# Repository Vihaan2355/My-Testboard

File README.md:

# My-Testboard

This repository contains the design files for a custom hardware development and test board built using KiCad. The circuit is designed around a standard LM555 testboard.

# Project Structure
* /CAD - Contains the 3D STEP file (TestBoard.step) of the populated PCB layout and the native project files.
* /GERBERS - Contains the production zip file (Gerbers.zip) required for manufacturing fabrication.
* TestBoard.csv - Bill of Materials (BOM) listing the complete component inventory and sourcing data.
* TestBoard-pos.csv - Component Placement List (CPL) detailing structural coordinate data for assembly alignment.
* TestBoard.pdf - Schematic drawing printout.

# Mechanical and Hardware Design
This project is a bare hardware development and test board. It focuses strictly on circuit traces and signal routing, and it does not feature a physical 3D-printed case, enclosure, or mechanical stand. 

The STEP file provided inside the /CAD folder represents the complete 3D spatial layout of the PCB alongside its mounted components. This file serves as the complete, self-contained physical project assembly to satisfy the 3D modeling submission rule.

# Component Sourcing and Assembly Plan
The circuit utilizes a through-hole design layout. Assembly is split between factory placement and manual desktop soldering:

* Integrated Circuit (U1): LM555CN  chip in a DIP-8 package.
* Potentiometer (RV1): 10K vertical rotary trimmer potentiometer (3386P package). This part is sourced via external vendor channels and will be hand-soldered locally.
* Passive Components (R1-R3, C1-C3, D1): 1K Ohm 1/4W axial resistors, ceramic disc capacitors (10nF and 100nF values), a radial electrolytic capacitor (47uF value), and a 3mm blue indicator LED. These parts are sourced via bulk electronic assortment kits and will be hand-soldered locally.
* Power Interface (J1): 2-pin horizontal screw terminal block featuring 3.5mm pad pitch spacing. This part is sourced via external vendor channels and will be hand-soldered locally.

# Manufacturing Fabrication
The bare boards will be manufactured using standard FR4 fiberglass substrate through JLCPCB using the production zip file in the gerbers directory. Remaining components will be manually populated, soldered, and verified on a test bench post-delivery.

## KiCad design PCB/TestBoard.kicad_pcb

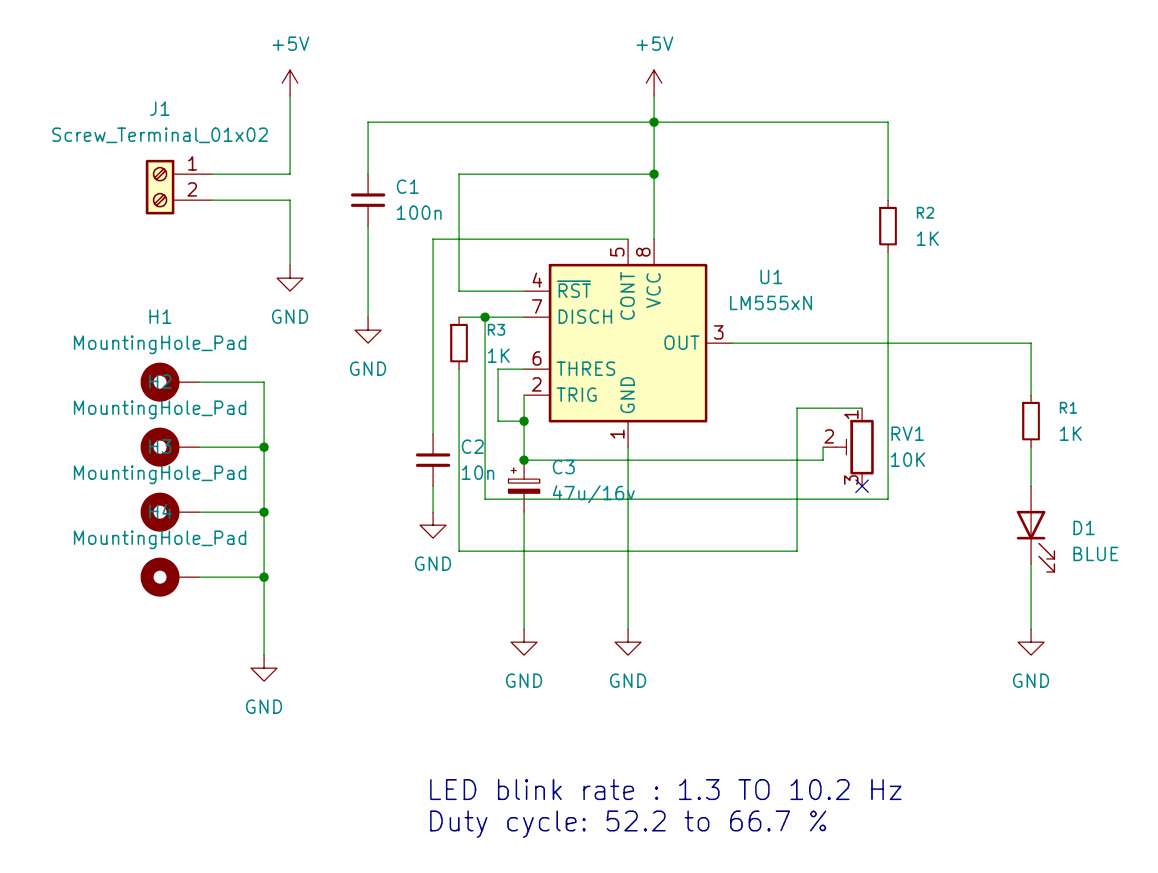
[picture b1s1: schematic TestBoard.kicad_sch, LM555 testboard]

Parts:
C1: 100n; C_Disc_D7.0mm_W2.5mm_P5.00mm
C2: 10n; C_Disc_D7.0mm_W2.5mm_P5.00mm
C3: 47u/16v; CP_Radial_D5.0mm_P2.50mm
D1: BLUE; LED_D3.0mm
H1, H2, H3, H4: MountingHole_Pad; MountingHole_3.2mm_M3_DIN965_Pad
J1: Screw_Terminal_01x02; TerminalBlock_Phoenix_PT-1,5-2-3.5-H_1x02_P3.50mm_Horizontal
R1, R2, R3: 1K; R_Axial_DIN0207_L6.3mm_D2.5mm_P10.16mm_Horizontal
RV1: 10K; Potentiometer_Bourns_3386P_Vertical
U1: LM555xN; DIP-8_W7.62mm

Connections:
+5V: C1.1, J1.1, R2.1, U1.4 (~RST), U1.8 (VCC)
GND: C1.2, C2.2, C3.2, D1.1 (K), H1.1 (1_1), H2.1 (1_1), H3.1 (1_1), H4.1 (1_1), J1.2, U1.1 (GND)
unnamed: D1.2 (A), R1.2
unnamed: R3.2, RV1.1
unnamed: C2.1, U1.5 (CONT)
unnamed: R2.2, R3.1, U1.7 (DISCH)
unnamed: R1.1, U1.3 (OUT)
unnamed: C3.1, RV1.2, U1.2 (TRIG), U1.6 (THRES)

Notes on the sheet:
LED blink rate : 1.3 TO 10.2 Hz Duty cycle: 52.2 to 66.7 %

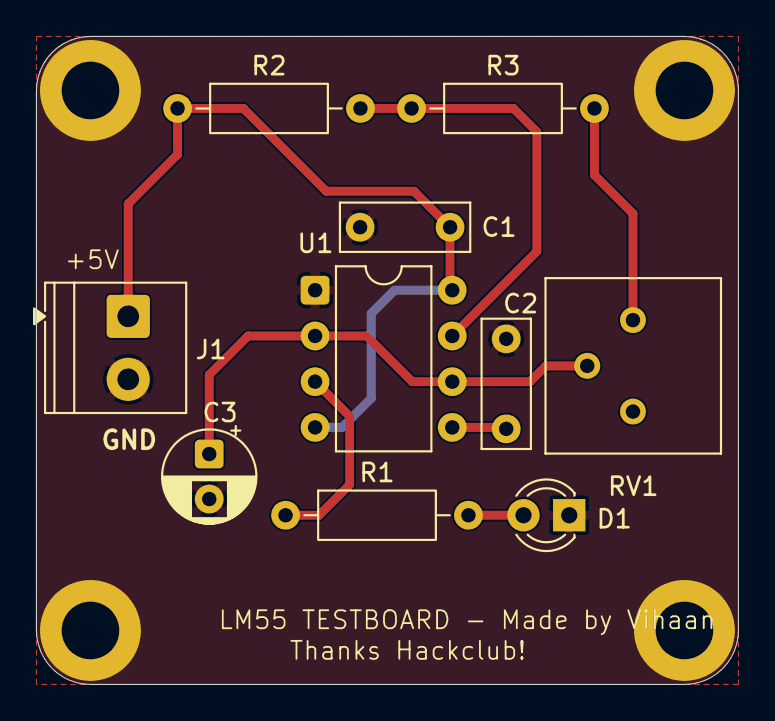
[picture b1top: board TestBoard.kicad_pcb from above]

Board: 2 copper layers, 39.0 x 36.0 mm, 14 parts (0 on the bottom side), 8 nets.
